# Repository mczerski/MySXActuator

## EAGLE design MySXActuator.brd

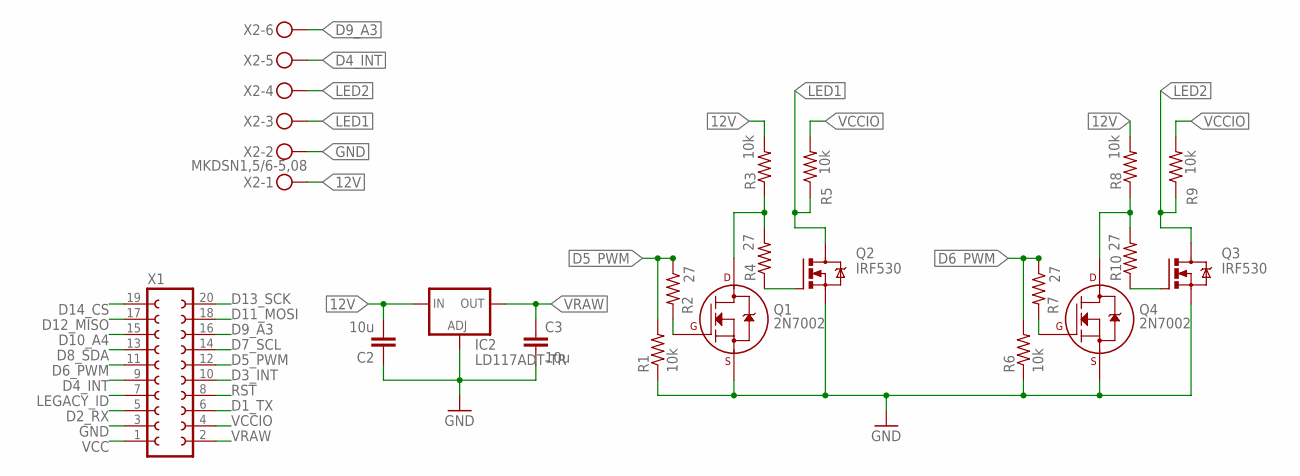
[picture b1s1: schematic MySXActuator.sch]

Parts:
C2: 10u; 1206
C3: 10u; 0603-CAP
IC2: LD117ADT-TR; DPACK
Q1, Q4: 2N7002; SOT-23
Q2, Q3: IRF530; TO220BV
R1, R3, R5, R6, R8, R9: 10k; 0603-RES
R2, R4, R7, R10: 27; 0603-RES
X1: FE10-2
X2: MKDSN1,5/6-5,08

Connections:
12V: C2.2, IC2.3 (IN), R3.2, R8.2, X2.1
D1_TX: X1.6
D2_RX: X1.5
D3_INT: X1.10
D4_INT: X1.9, X2.5
D5_PWM: R1.2, R2.1, X1.12
D6_PWM: R6.2, R7.1, X1.11
D7_SCL: X1.14
D8_SDA: X1.13
D9_A3: X1.16, X2.6
D10_A4: X1.15
D11_MOSI: X1.18
D12_MISO: X1.17
D13_SCK: X1.20
D14_CS: X1.19
GND: C2.1, C3.2, IC2.1 (ADJ), Q1.2 (S), Q2.S, Q3.S, Q4.2 (S), R1.1, R6.1, X1.3, X2.2
LED1: Q2.D, R5.1, X2.3
LED2: Q3.D, R9.1, X2.4
LEGACY_ID: X1.7
unnamed: Q4.1 (G), R7.2
unnamed: Q4.3 (D), R8.1, R10.2
unnamed: Q3.G, R10.1
unnamed: Q1.1 (G), R2.2
unnamed: Q1.3 (D), R3.1, R4.2
unnamed: Q2.G, R4.1
RST: X1.8
VCC: X1.1
VCCIO: R5.2, R9.2, X1.4
VRAW: C3.1, IC2.4 (OUT), X1.2

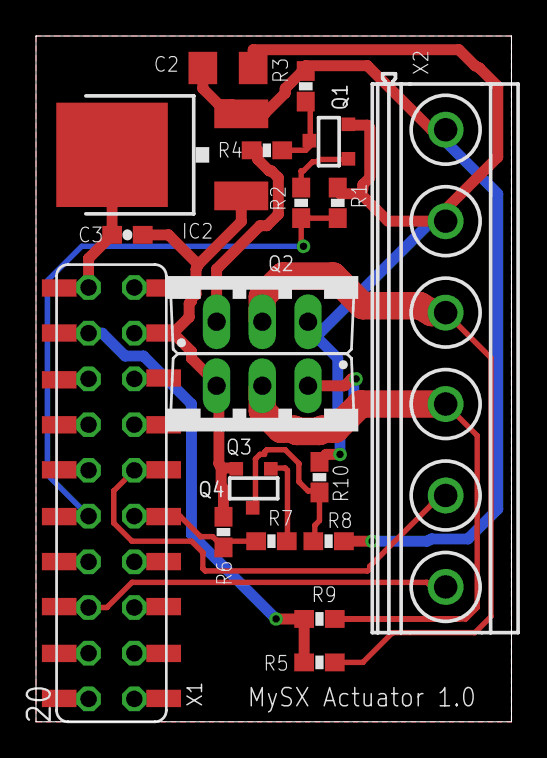
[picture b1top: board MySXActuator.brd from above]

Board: 2 copper layers, 26.4 x 38.1 mm, 19 parts (0 on the bottom side), 16 nets.

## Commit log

2019-03-27 initial commit, v1.0
2019-03-27 remove transistor value
2019-03-31 enlarge traces widths + add ldo
2019-04-03 add second dimmer
2019-04-04 fix stencil
2024-05-04 imported from eagle, ldo changed to buck converter
2024-05-05 change C2 footprint from 0201 to 0402
2024-05-05 add screenshot of the board
2024-05-25 refactor schematic to use kicad native symbols and footprints
2024-06-08 add reverse polarity protection and overvoltage protection for input pins
2024-07-26 add schematic export
2024-07-27 update schematic
    - add zener diode to protect high positive voltage on inputs
    - add anoter 2 input sections as alternative to led drivers
    - add add rj45 socket for i2c interface
2024-07-27 update PCB after schematic changes
2024-09-18 Add removed buck converter
    - previously removed buck converter is needed to not require power from
    RS485 line
    - position RJ45 connector closer to center of the board to allow use
    straigth connector (facing up)
    - replace THT power transistors with SMT power transistors
2026-06-11 add input voltage transient protection
2026-06-14 add resistors to prevent led glowing when turned off

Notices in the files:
parts and their libraries:
SparkFun-Passives: Licensing: Creative Commons ShareAlike 4.0 International - https://creativecommons.org/licenses/by-sa/4.0
